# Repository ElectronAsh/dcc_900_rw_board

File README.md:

# dcc_900_rw_board

This is currently UNFINISHED.

The libraries for the TDA1316 and TDA1317 are done, but more passives and smaller components need to be added.

The schematic for the TDA and logic chips isn't finished yet either.

Use freely, but at your own risk!

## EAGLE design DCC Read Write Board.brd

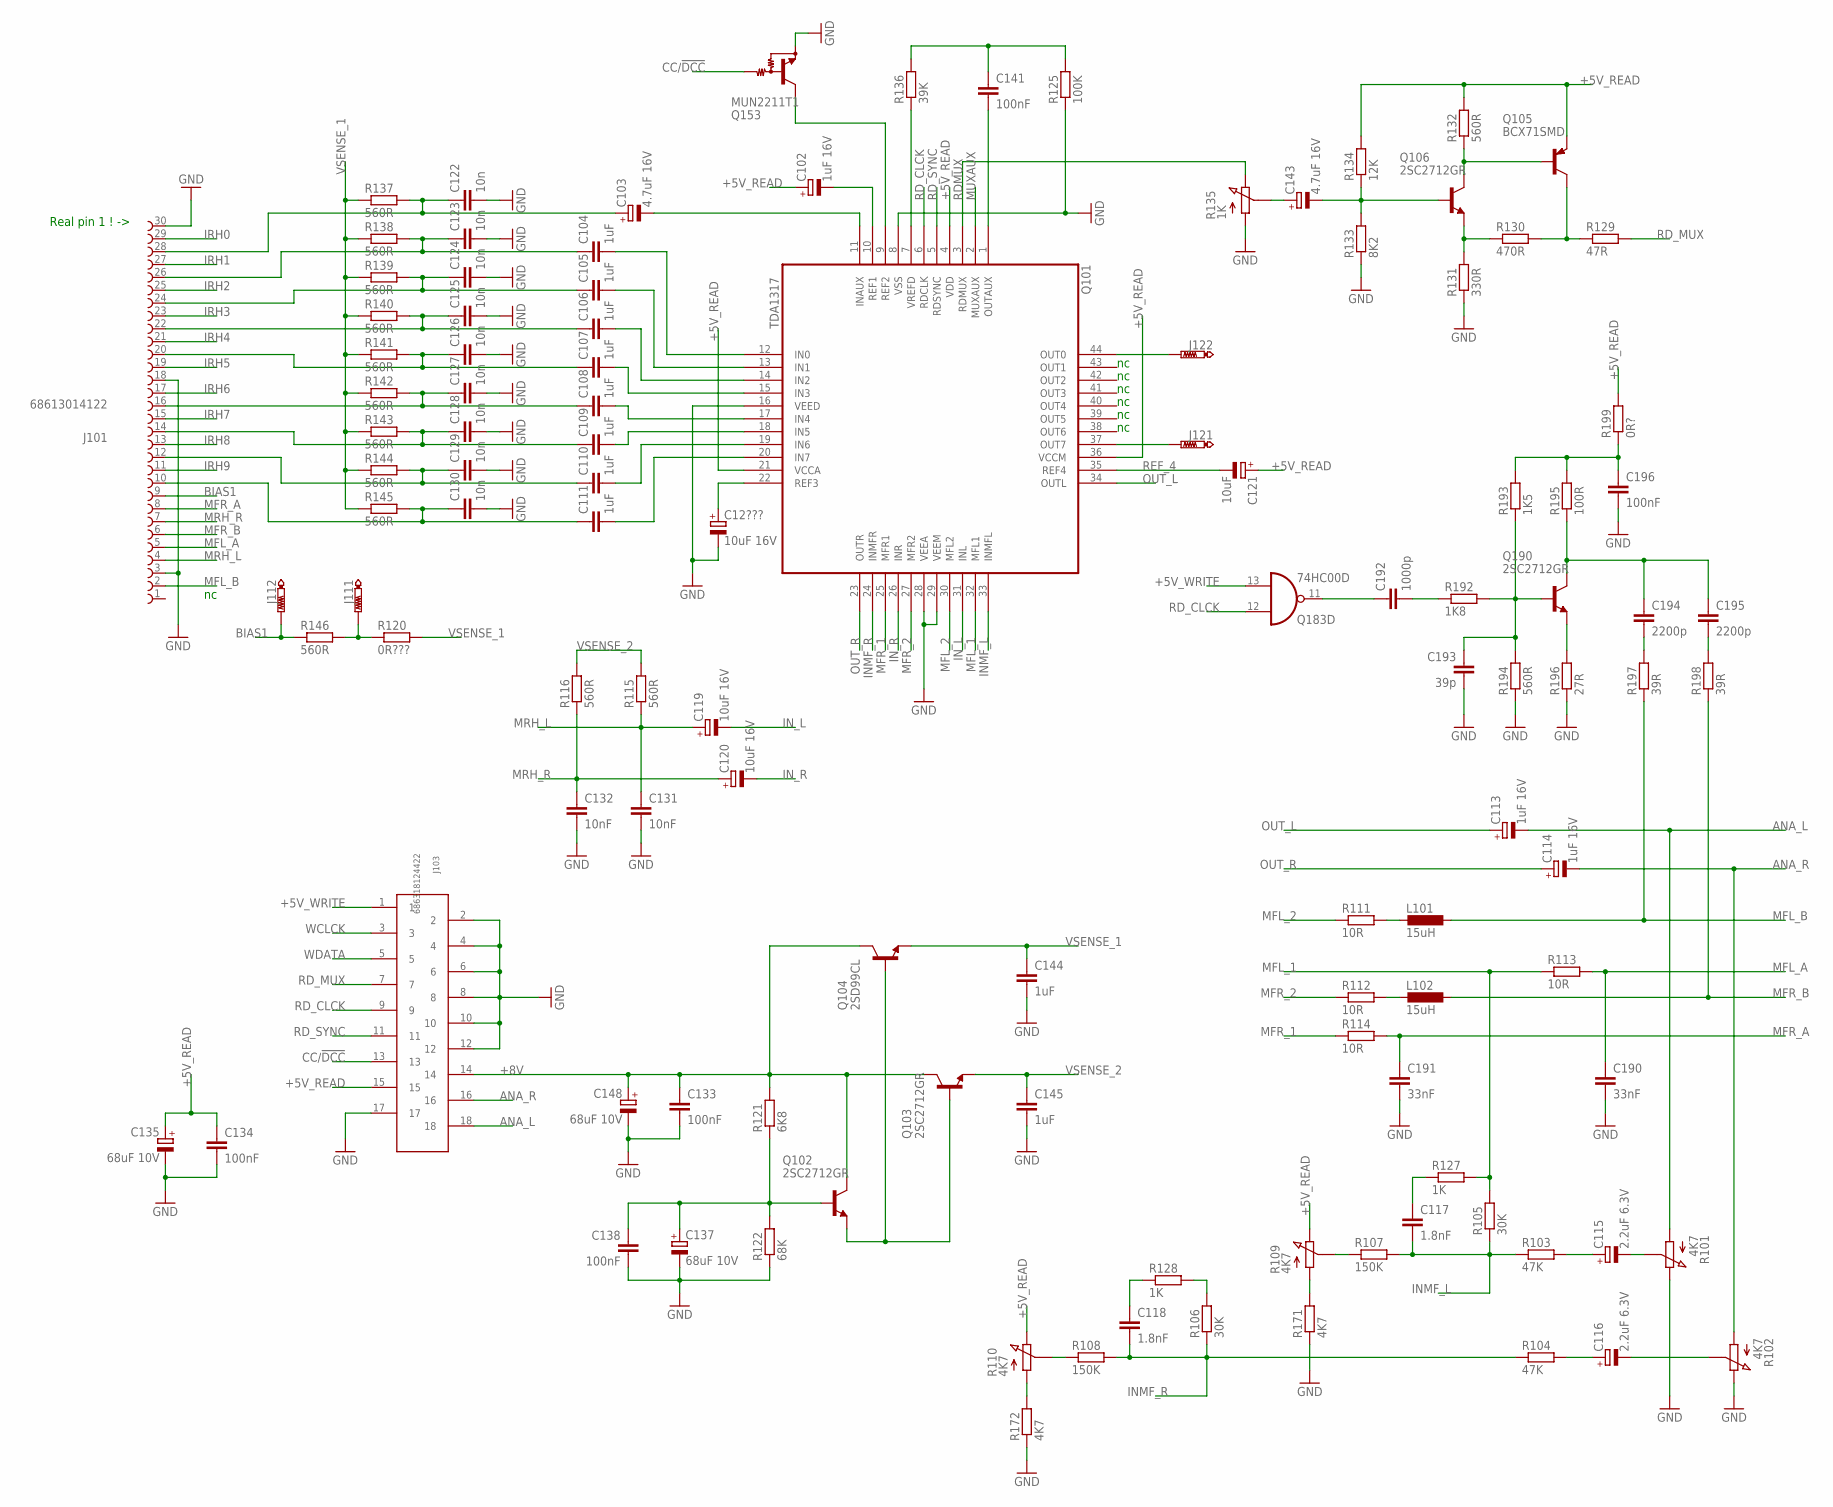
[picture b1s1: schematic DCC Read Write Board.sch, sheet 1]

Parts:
C12???, C119, C120: 10uF 16V; 153CLV-0505
C102, C113, C114: 1uF 16V; B/3528-21W
C103, C143: 4.7uF 16V; 153CLV-0505
C104, C105, C106, C107, C108, C109, C110, C111, C144, C145: 1uF; C0603
C115, C116: 2.2uF 6.3V; C/6032-28R
C117, C118: 1.8nF; C0603
C121: 10uF; 153CLV-0505
C122, C123, C124, C125, C126, C127, C128, C129, C130: 10n; C0603
C131, C132: 10nF; C0603
C133, C134, C138, C141, C196: 100nF; C0603
C135, C137, C148: 68uF 10V; PANASONIC_E
C190, C191: 33nF; C0603
C192: 1000p; C0603
C193: 39p; C0603
C194, C195: 2200p; C0603
J101: 68613014122
J103: 686318124422
J111, J112, J121, J122: PTR1TP18SQ; TP18SQ
L101, L102: 15uH; L1812
Q101: TDA1317; QFP44
Q102, Q103, Q106, Q190: 2SC2712GR; SOT23-BEC
Q104: 2SD99CL; SOT23-BEC
Q105: BCX71SMD; SOT23
Q153: MUN2211T1; SC59-BEC
Q183: 74HC00D; SO14
R101, R102, R109, R110: 4K7; PC25
R103, R104: 47K; R0603
R105, R106: 30K; R0603
R107, R108: 150K; R0603
R111, R112, R113, R114: 10R; R0603
R115, R116, R132, R137, R138, R139, R140, R141, R142, R143, R144, R145, R146, R194: 560R; R0603
R120: 0R???; R0603
R121: 6K8; R0603
R122: 68K; R0603
R125: 100K; R0603
R127, R128: 1K; R0603
R129: 47R; R0603
R130: 470R; R0603
R131: 330R; R0603
R133: 8K2; R0603
R134: 12K; R0603
R135: 1K; PC25
R136: 39K; R0603
R171, R172: 4K7; R0603
R192: 1K8; R0603
R193: 1K5; R0603
R195: 100R; R0603
R196: 27R; R0603
R197, R198: 39R; R0603
R199: 0R?; R0603

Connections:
+5V_READ: C102.+, C121.+, C134.1, C135.+, J103.15, Q101.4 (VDD), Q101.21 (VCCA), Q101.36 (VCCM), Q105.2 (E), R109.E, R110.E, R132.2, R134.2, R199.2
+5V_WRITE: J103.1, Q183.13 (I1); also elsewhere on the board
+8V: C133.1, C148.+, J103.14, Q102.C, Q103.C, Q104.C, R121.2
ANA_L: C113.-, J103.18, R101.A
ANA_R: C114.-, J103.16, R102.A
BIAS1: J101.9, J112.TP, R146.1
CC/!DCC: J103.13, Q153.B
GND: C12???.-, C122.2, C123.2, C124.2, C125.2, C126.2, C127.2, C128.2, C129.2, C130.2, C131.2, C132.2, C133.2, C134.2, C135.-, C137.-, C138.2, C144.2, C145.2, C148.-, C190.2, C191.2, C193.2, C196.2, J101.3, J101.18, J101.30, J103.2, J103.4, J103.6, J103.8, J103.10, J103.12, J103.17, Q101.8 (VSS), Q101.16 (VEED), Q101.28 (VEEA), Q101.29 (VEEM), Q153.E, R101.E, R102.E, R122.1, R125.1, R131.1, R133.1, R135.A, R171.1, R172.1, R194.1, R196.1; also elsewhere on the board
INMF_L: C117.2, Q101.33 (INMFL), R103.1, R105.1, R107.2
INMF_R: C118.2, Q101.24 (INMFR), R104.1, R106.1, R108.2
IN_L: C119.-, Q101.31 (INL)
IN_R: C120.-, Q101.26 (INR)
IRH0: J101.29; also elsewhere on the board
IRH1: J101.27; also elsewhere on the board
IRH2: J101.25; also elsewhere on the board
IRH3: J101.23; also elsewhere on the board
IRH4: J101.21; also elsewhere on the board
IRH5: J101.19; also elsewhere on the board
IRH6: J101.17; also elsewhere on the board
IRH7: J101.15; also elsewhere on the board
IRH8: J101.13; also elsewhere on the board
IRH9: J101.11; also elsewhere on the board
MFL_1: Q101.32 (MFL1), R105.2, R113.1, R127.2
MFL_2: Q101.30 (MFL2), R111.1
MFL_3: R106.2, R128.2
MFL_A: C190.1, J101.5, R113.2
MFL_B: J101.2, L101.1, R197.1
MFR_1: Q101.25 (MFR1), R114.1
MFR_2: Q101.27 (MFR2), R112.1
MFR_A: C191.1, J101.8, R114.2
MFR_B: J101.6, L102.1, R198.1
MRH_L: C119.+, C131.1, J101.4, R115.1
MRH_R: C120.+, C132.1, J101.7, R116.1
MUXAUX: Q101.2 (MUXAUX)
unnamed: C111.2, Q101.20 (IN7)
unnamed: C110.2, Q101.19 (IN6)
unnamed: C109.2, Q101.18 (IN5)
unnamed: C108.2, Q101.17 (IN4)
unnamed: C107.2, Q101.15 (IN3)
unnamed: C106.2, Q101.14 (IN2)
unnamed: C105.2, Q101.13 (IN1)
unnamed: C104.2, Q101.12 (IN0)
unnamed: C103.-, Q101.11 (INAUX)
unnamed: C111.1, C130.1, J101.10, R145.2
unnamed: C110.1, C129.1, J101.12, R144.2
unnamed: C109.1, C128.1, J101.14, R143.2
unnamed: C108.1, C127.1, J101.16, R142.2
unnamed: C107.1, C126.1, J101.20, R141.2
unnamed: C106.1, C125.1, J101.22, R140.2
unnamed: C105.1, C124.1, J101.24, R139.2
unnamed: C104.1, C123.1, J101.26, R138.2
unnamed: C103.+, C122.1, J101.28, R137.2
unnamed: Q101.9 (REF2), Q153.C
unnamed: Q102.E, Q103.B, Q104.B
unnamed: C137.+, C138.1, Q102.B, R121.1, R122.2
unnamed: C102.-, Q101.10 (REF1)
unnamed: C141.2, Q101.1 (OUTAUX)
unnamed: Q101.7 (VREFD), R136.1
unnamed: C141.1, R125.2, R136.2
unnamed: C12???.+, Q101.22 (REF3)
unnamed: C192.1, Q183.11 (O)
unnamed: C192.2, R192.1
unnamed: C196.1, R193.2, R195.2, R199.1
unnamed: C193.1, Q190.B, R192.2, R193.1, R194.2
unnamed: C194.1, C195.1, Q190.C, R195.1
unnamed: Q190.E, R196.2
unnamed: C195.2, R198.2
unnamed: C194.2, R197.2
unnamed: L102.2, R112.2
unnamed: L101.2, R111.2
unnamed: J122.TP, Q101.44 (OUT0)
unnamed: J121.TP, Q101.37 (OUT7)
unnamed: J111.TP, R120.1, R146.2
unnamed: C115.-, R101.S
unnamed: C116.-, R102.S
unnamed: C115.+, R103.2
unnamed: C116.+, R104.2
unnamed: C143.-, Q106.B, R133.2, R134.1
unnamed: C117.1, R127.1
unnamed: R107.1, R109.S
unnamed: Q106.E, R130.1, R131.2
unnamed: C118.1, R128.1
unnamed: R108.1, R110.S
unnamed: R109.A, R171.2
unnamed: R110.A, R172.2
unnamed: Q105.1 (B), Q106.C, R132.1
unnamed: Q105.3 (C), R129.1, R130.2
unnamed: C143.+, R135.S
OUT_L: C113.+, Q101.34 (OUTL)
OUT_R: C114.+, Q101.23 (OUTR)
RDMUX: Q101.3 (RDMUX), R135.E
RD_CLCK: J103.9, Q101.6 (RDCLK), Q183.12 (I0)
RD_MUX: J103.7, R129.2
RD_SYNC: J103.11, Q101.5 (RDSYNC)
REF_4: C121.-, Q101.35 (REF4)
VSENSE_1: C144.1, Q104.E, R120.2, R137.1, R138.1, R139.1, R140.1, R141.1, R142.1, R143.1, R144.1, R145.1
VSENSE_2: C145.1, Q103.E, R115.2, R116.2
WCLCK: J103.3; also elsewhere on the board
WDATA: J103.5; also elsewhere on the board

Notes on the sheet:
Real pin 1 ! ->

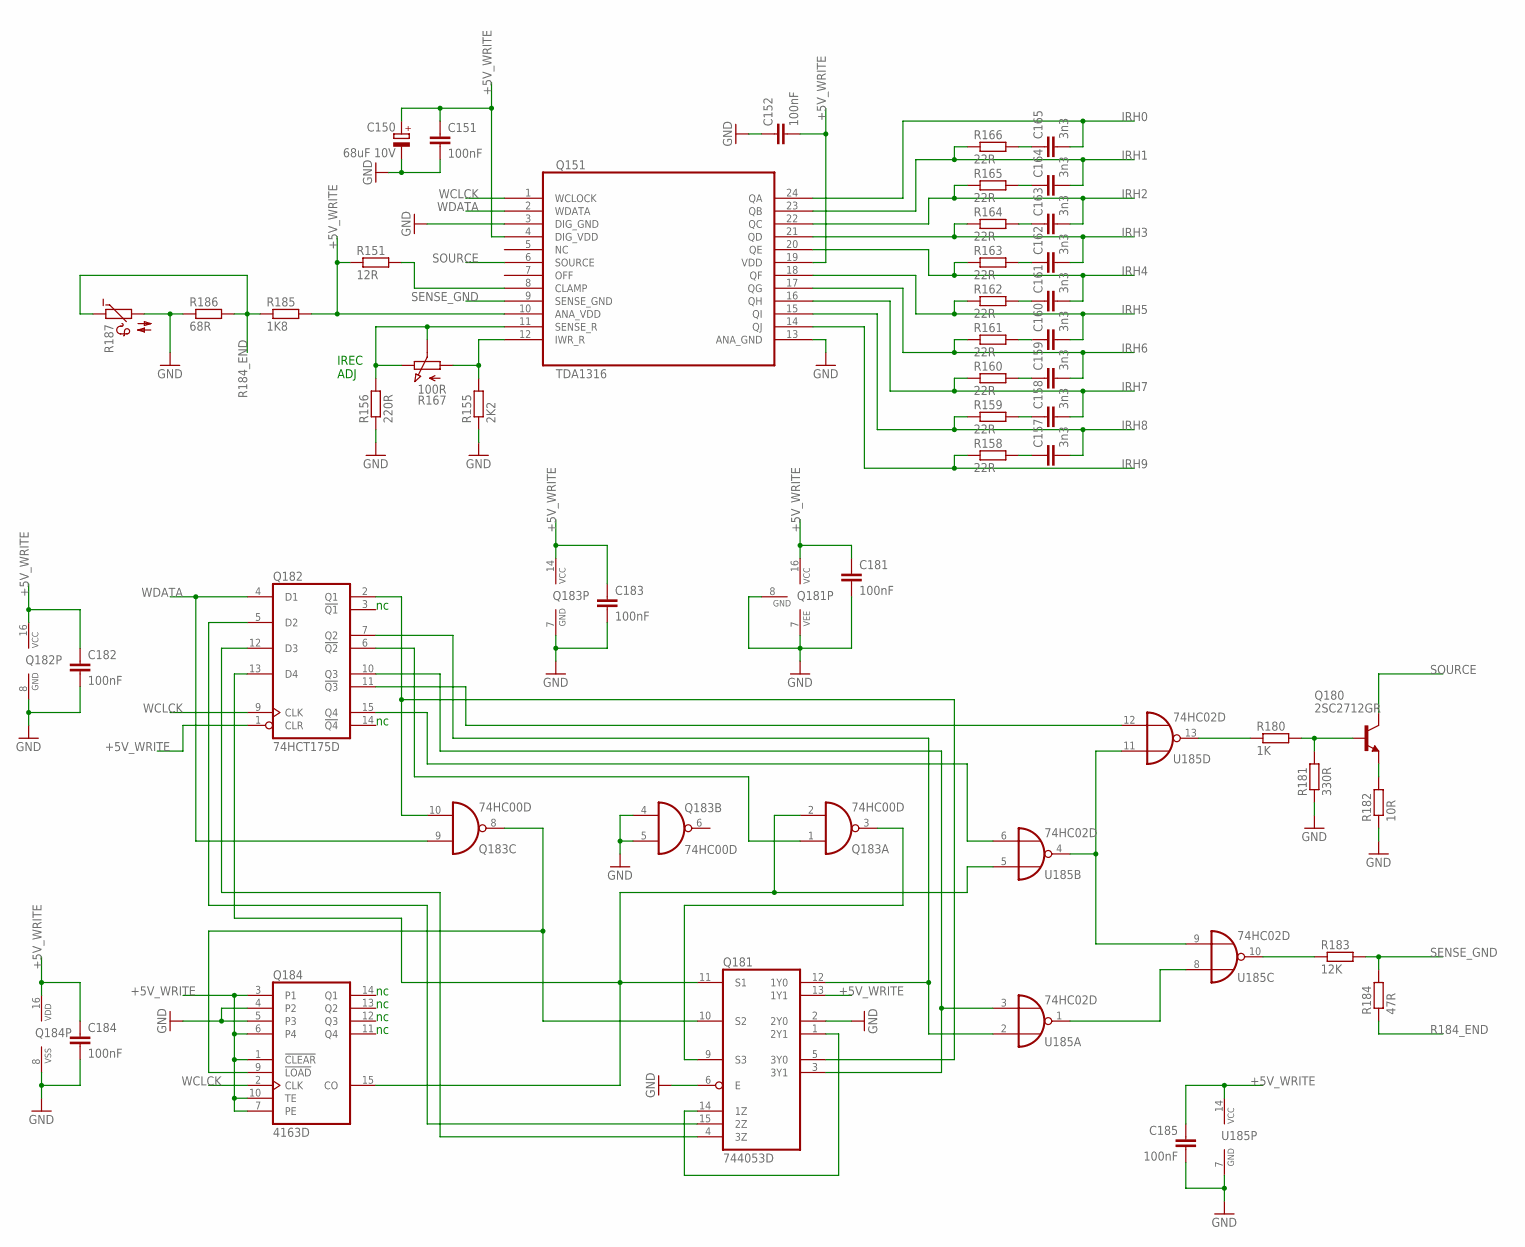
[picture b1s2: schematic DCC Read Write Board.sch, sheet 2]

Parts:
C150: 68uF 10V; PANASONIC_E
C151, C152, C181, C182, C183, C184, C185: 100nF; C0603
C157, C158, C159, C160, C161, C162, C163, C164, C165: 3n3; C0603
Q151: TDA1316; SO24L
Q180: 2SC2712GR; SOT23-BEC
Q181: 744053D; SO16
Q182: 74HCT175D; SO16
Q183: 74HC00D; SO14
Q184: 4163D; SO16
R151: 12R; R0603
R155: 2K2; R0603
R156: 220R; R0603
R158, R159, R160, R161, R162, R163, R164, R165, R166: 22R; R0603
R167: 100R; PC25
R180: 1K; R0603
R181: 330R; R0603
R182: 10R; R0603
R183: 12K; R0603
R184: 47R; R0603
R185: 1K8; R0603
R186: 68R; R0603
R187: B57164
U185: 74HC02D; SO14

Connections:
+5V_WRITE: C150.+, C151.1, C152.2, C181.1, C182.1, C183.1, C184.1, C185.1, Q151.4 (DIG_VDD), Q151.10 (ANA_VDD), Q151.19 (VDD), Q181.13 (1Y1), Q181.16 (VCC), Q182.1 (CLR), Q182.16 (VCC), Q183.14 (VCC), Q184.1 (!CLEAR), Q184.3 (P1), Q184.6 (P4), Q184.7 (PE), Q184.10 (TE), Q184.16 (VDD), R151.1, R185.2, U185.14 (VCC); also elsewhere on the board
GND: C150.-, C151.2, C152.1, C181.2, C182.2, C183.2, C184.2, C185.2, Q151.3 (DIG_GND), Q151.13 (ANA_GND), Q181.2 (2Y0), Q181.6 (E), Q181.7 (VEE), Q181.8 (GND), Q182.8 (GND), Q183.4 (I0), Q183.5 (I1), Q183.7 (GND), Q184.4 (P2), Q184.5 (P3), Q184.8 (VSS), R155.1, R156.1, R181.1, R182.1, R186.1, R187.2, U185.7 (GND); also elsewhere on the board
IRH0: C165.2, Q151.24 (QA); also elsewhere on the board
IRH1: C164.2, Q151.23 (QB), R166.1; also elsewhere on the board
IRH2: C163.2, Q151.22 (QC), R165.1; also elsewhere on the board
IRH3: C162.2, Q151.21 (QD), R164.1; also elsewhere on the board
IRH4: C161.2, Q151.20 (QE), R163.1; also elsewhere on the board
IRH5: C160.2, Q151.18 (QF), R162.1; also elsewhere on the board
IRH6: C159.2, Q151.17 (QG), R161.1; also elsewhere on the board
IRH7: C158.2, Q151.16 (QH), R160.1; also elsewhere on the board
IRH8: C157.2, Q151.15 (QI), R159.1; also elsewhere on the board
IRH9: Q151.14 (QJ), R158.1; also elsewhere on the board
unnamed: Q181.10 (S2), Q183.8 (O), Q184.9 (!LOAD)
unnamed: Q181.5 (3Y0), Q182.2 (Q1), Q183.10 (I1)
unnamed: Q181.11 (S1), Q182.13 (D4), Q183.2 (I1), Q184.15 (CO), U185.5 (I0)
unnamed: Q181.15 (2Z), Q182.5 (D2)
unnamed: Q181.9 (S3), Q183.3 (O)
unnamed: Q182.6 (!Q2), Q183.1 (I0)
unnamed: Q182.15 (Q4), U185.6 (I1)
unnamed: U185.4 (O), U185.9 (I1), U185.11 (I0)
unnamed: Q181.3 (3Y1), Q182.10 (Q3), U185.3 (I1)
unnamed: Q181.1 (2Y1), Q181.14 (1Z)
unnamed: C165.1, R166.2
unnamed: C164.1, R165.2
unnamed: C163.1, R164.2
unnamed: C162.1, R163.2
unnamed: C161.1, R162.2
unnamed: C160.1, R161.2
unnamed: C159.1, R160.2
unnamed: C158.1, R159.2
unnamed: C157.1, R158.2
unnamed: Q181.12 (1Y0), Q182.7 (Q2), U185.2 (I0)
unnamed: U185.1 (O), U185.8 (I0)
unnamed: Q182.11 (!Q3), U185.12 (I1)
unnamed: Q181.4 (3Z), Q182.12 (D3)
unnamed: R183.1, U185.10 (O)
unnamed: R180.1, U185.13 (O)
unnamed: Q180.B, R180.2, R181.2
unnamed: Q180.E, R182.2
unnamed: Q151.11 (SENSE_R), R156.2, R167.E, R167.S
unnamed: Q151.12 (IWR_R), R155.2, R167.A
unnamed: Q151.8 (CLAMP), R151.2
R184_END: R184.1, R185.1, R186.2, R187.1
SENSE_GND: Q151.9 (SENSE_GND), R183.2, R184.2
SOURCE: Q151.6 (SOURCE), Q180.C
WCLCK: Q151.1 (WCLOCK), Q182.9 (CLK), Q184.2 (CLK); also elsewhere on the board
WDATA: Q151.2 (WDATA), Q182.4 (D1), Q183.9 (I0); also elsewhere on the board

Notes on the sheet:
IREC ADJ

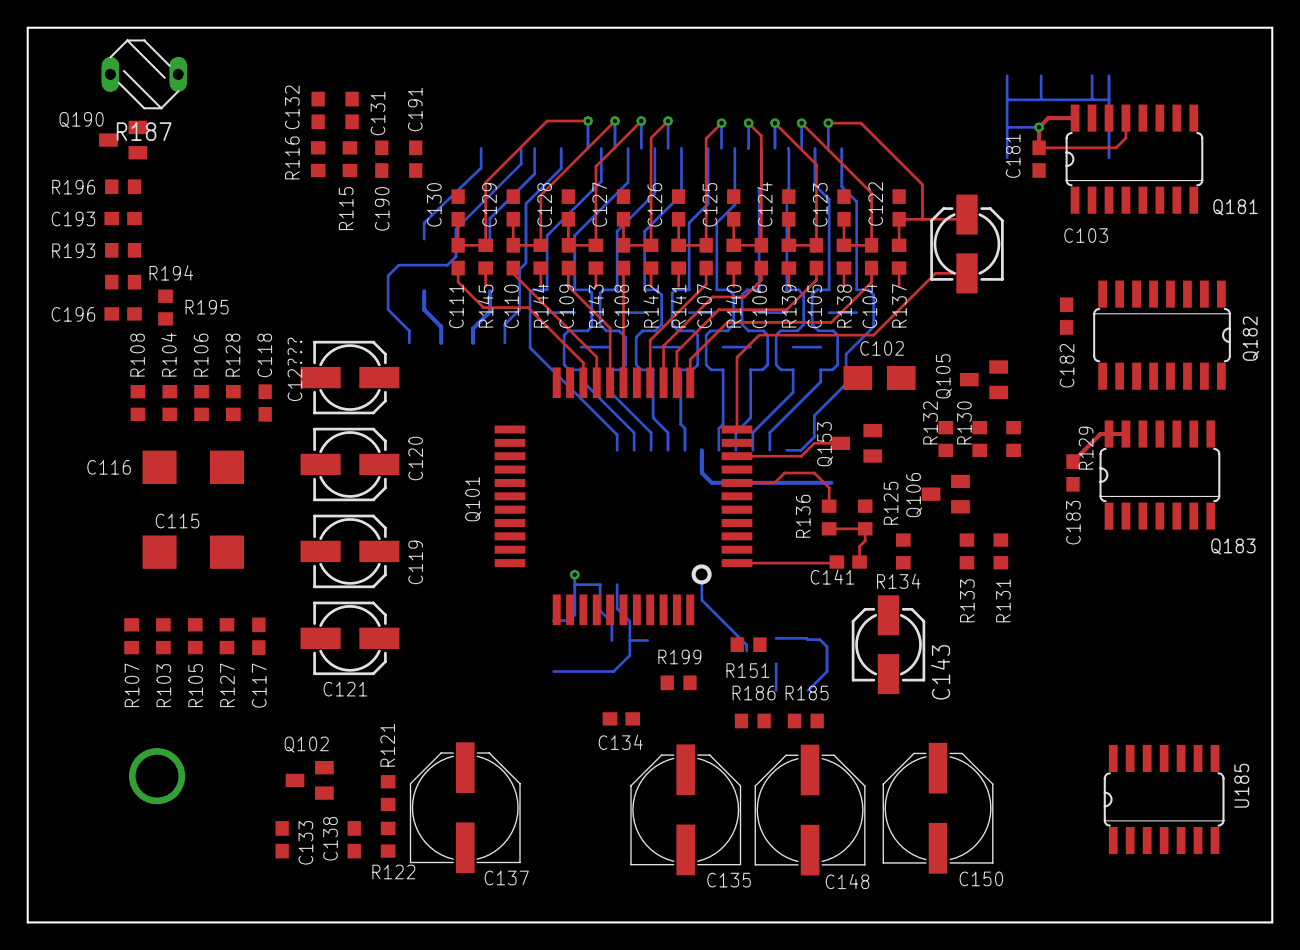
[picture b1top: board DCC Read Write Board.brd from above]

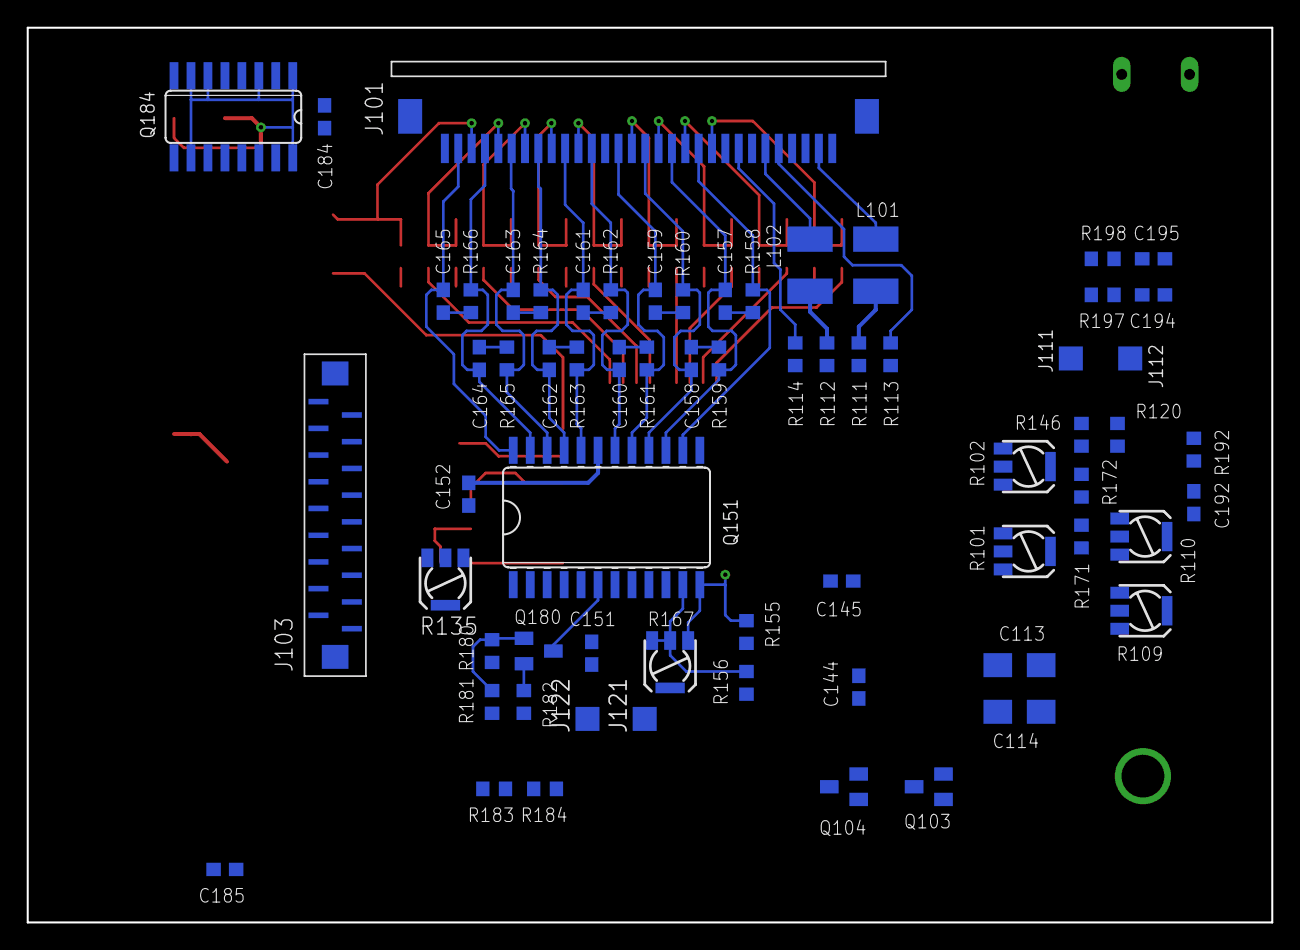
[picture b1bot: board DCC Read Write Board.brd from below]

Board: 2 copper layers, 93.2 x 67.0 mm, 159 parts (66 on the bottom side), 131 nets.

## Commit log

2023-01-11 Added sch and brd files
2023-01-13 Most of the Write amp and logic gate schematic done
2023-01-13 Everything added to schematic, but needs checking
2023-01-13 Schematic complete. Still needs checking
2023-01-13 Started placing more passives
2023-01-14 Initial parts placement done

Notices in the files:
parts and their libraries:
FPC_Connectors_Flat_Flexible_Cable_rev15: Copyright: Würth Elektronik
